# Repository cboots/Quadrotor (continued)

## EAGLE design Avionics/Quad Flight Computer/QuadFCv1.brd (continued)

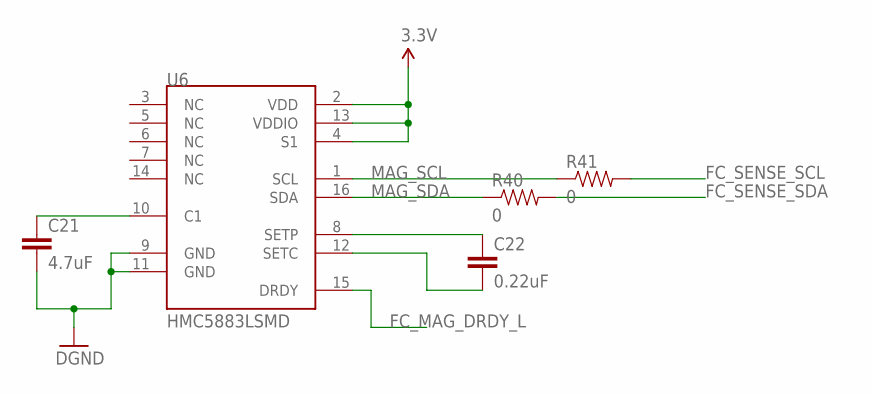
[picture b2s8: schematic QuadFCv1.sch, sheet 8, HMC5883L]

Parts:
C21: 4.7uF; 0402-CAP
C22: 0.22uF; 0402-CAP
R40, R41: 0; 0402-RES
U6: HMC5883LSMD; 16LPCC

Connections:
3.3V: U6.2 (VDD), U6.4 (S1), U6.13 (VDDIO); also elsewhere on the board
FC_MAG_DRDY_L: U6.15 (DRDY); also elsewhere on the board
FC_SENSE_SCL: R41.2; also elsewhere on the board
FC_SENSE_SDA: R40.2; also elsewhere on the board
GND: C21.2, U6.9 (GND), U6.11 (GND); also elsewhere on the board
MAG_SCL: R41.1, U6.1 (SCL); also elsewhere on the board
MAG_SDA: R40.1, U6.16 (SDA); also elsewhere on the board
unnamed: C21.1, U6.10 (C1)
unnamed: C22.1, U6.8 (SETP)
unnamed: C22.2, U6.12 (SETC)

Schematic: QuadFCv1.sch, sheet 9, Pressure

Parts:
C23: 0.1uF; 0402-CAP
U7: MS5611-01BA

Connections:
3.3V: C23.1, U7.1 (VDD), U7.2 (PS); also elsewhere on the board
FC_SENSE_SCL: U7.8 (SCLK); also elsewhere on the board
FC_SENSE_SDA: U7.7 (SDI/SDA); also elsewhere on the board
GND: C23.2, U7.3 (GND), U7.5 (CSB2); also elsewhere on the board

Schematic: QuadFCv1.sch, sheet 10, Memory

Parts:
J2: 1050270001
U8: 74AUP1G19GW; SOT363_PHILIPS
U9: S25FL127S; SOIC8

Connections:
3.3V: J2.P4 (VDD), U8.5 (VCC), U9.8 (VCC); also elsewhere on the board
FC_MEM_CLK: J2.P5 (SCLK), U9.6 (SCK); also elsewhere on the board
FC_MEM_FSS: U8.3 (EN_L); also elsewhere on the board
FC_MEM_MISO: J2.P7 (DAT0/DO), U9.2 (SO); also elsewhere on the board
FC_MEM_MOSI: J2.P3 (CMD/DI), U9.5 (SI); also elsewhere on the board
FC_MEM_SEL: U8.1 (SEL); also elsewhere on the board
FC_SD_PRESENT: J2.G1 (SWITCH); also elsewhere on the board
FLASH_CS_L: U8.6 (1Y), U9.1 (CS_L)
GND: J2.P6 (VSS1), U8.2 (GND), U9.4 (GND); also elsewhere on the board
SD_CS_L: J2.P2 (CD/DAT3/CS), U8.4 (2Y)

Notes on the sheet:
Internal Pullups

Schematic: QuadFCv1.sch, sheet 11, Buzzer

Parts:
BZR: CMT-1203-SMT
R57: 0; 0402-RES
R58, R59: 10K; 0402-RES
U4: MCP6L91T-E/OT; SOT23-5

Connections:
3.3V: R58.2; also elsewhere on the board
5V: U4.5 (V+); also elsewhere on the board
BUZZER_PWM: U4.3 (+IN); also elsewhere on the board
GND: BZR.P$2 (2), R59.1, U4.2 (V-); also elsewhere on the board
unnamed: R57.1, U4.1 (OUT)
unnamed: BZR.P$1 (1), R57.2
unnamed: R58.1, R59.2, U4.4 (-IN)

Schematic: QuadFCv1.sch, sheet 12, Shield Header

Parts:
JP1: M101X10-SMT-0.05; 1X10_SMT-0.05
JP2, JP3, JP4: M12; 1X12_SMT-0.05

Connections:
3.3V: JP3.2; also elsewhere on the board
5V: JP3.1; also elsewhere on the board
BUZZER_PWM: JP1.5; also elsewhere on the board
FC_IMU_MISO: JP2.2; also elsewhere on the board
FC_IMU_MOSI: JP2.1; also elsewhere on the board
FC_IMU_SCLK: JP2.3; also elsewhere on the board
FC_JTAG_TCK: JP4.5; also elsewhere on the board
FC_JTAG_TDI: JP4.7; also elsewhere on the board
FC_JTAG_TDO: JP4.8; also elsewhere on the board
FC_JTAG_TMS: JP4.6; also elsewhere on the board
FC_MEM_CLK: JP3.4; also elsewhere on the board
FC_MEM_MISO: JP3.5; also elsewhere on the board
FC_MEM_MOSI: JP3.3; also elsewhere on the board
FC_PB2: JP4.12; also elsewhere on the board
FC_PB3: JP4.11; also elsewhere on the board
FC_PB4: JP4.1; also elsewhere on the board
FC_PB5: JP4.2; also elsewhere on the board
FC_PD0: JP3.9; also elsewhere on the board
FC_PD1: JP3.8; also elsewhere on the board
FC_PD2: JP3.7; also elsewhere on the board
FC_PD3: JP3.6; also elsewhere on the board
FC_PD4: JP3.12; also elsewhere on the board
FC_PE4: JP3.10; also elsewhere on the board
FC_PE5: JP3.11; also elsewhere on the board
FC_PF0: JP2.5; also elsewhere on the board
FC_PF1: JP2.6; also elsewhere on the board
FC_PF2: JP2.7; also elsewhere on the board
FC_PF3: JP2.8; also elsewhere on the board
FC_PF4: JP2.4; also elsewhere on the board
FC_PG2: JP2.10; also elsewhere on the board
FC_PG3: JP2.9; also elsewhere on the board
FC_PG4: JP4.10; also elsewhere on the board
FC_PG5: JP4.9; also elsewhere on the board
FC_PG6: JP4.4; also elsewhere on the board
FC_PG7: JP4.3; also elsewhere on the board
FC_RESET_L: JP1.10; also elsewhere on the board
FC_SENSE_SCL: JP2.11; also elsewhere on the board
FC_SENSE_SDA: JP2.12; also elsewhere on the board
GND: JP1.1, JP1.2; also elsewhere on the board
GPS_RX: JP1.6; also elsewhere on the board
GPS_TX: JP1.7; also elsewhere on the board
RADIO_RX: JP1.3; also elsewhere on the board
RADIO_TX: JP1.4; also elsewhere on the board

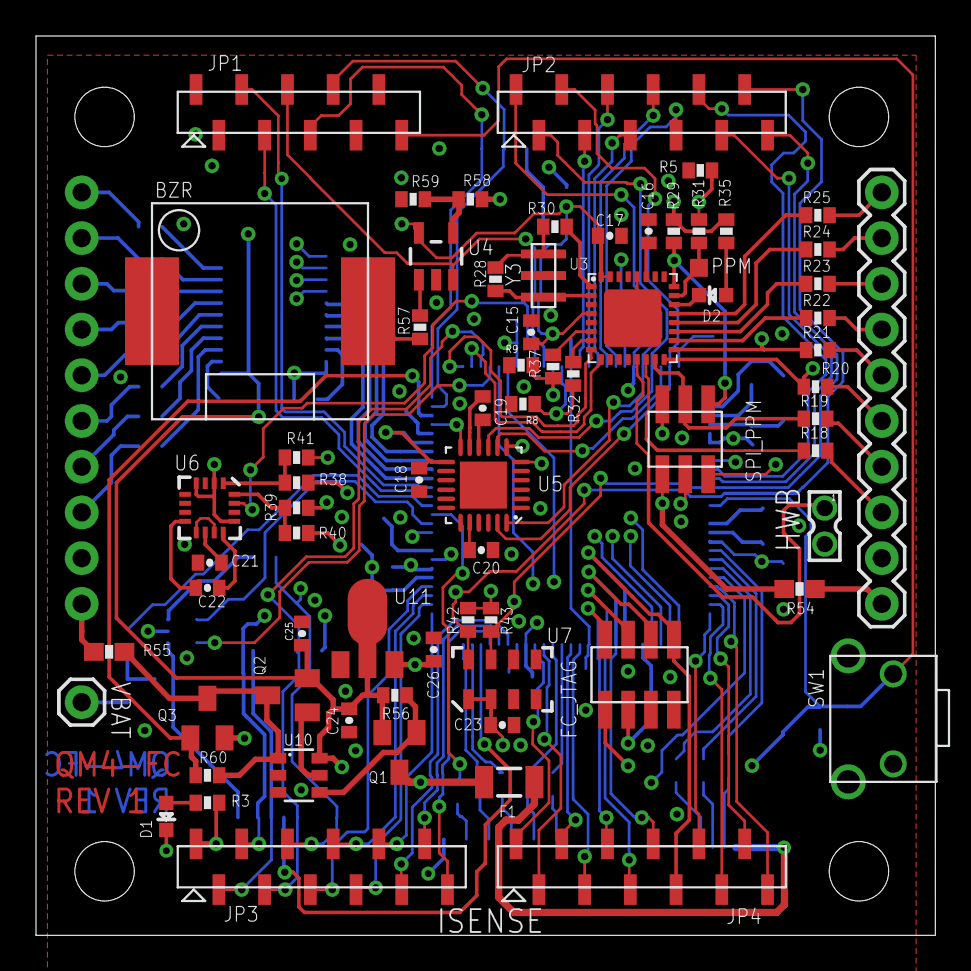
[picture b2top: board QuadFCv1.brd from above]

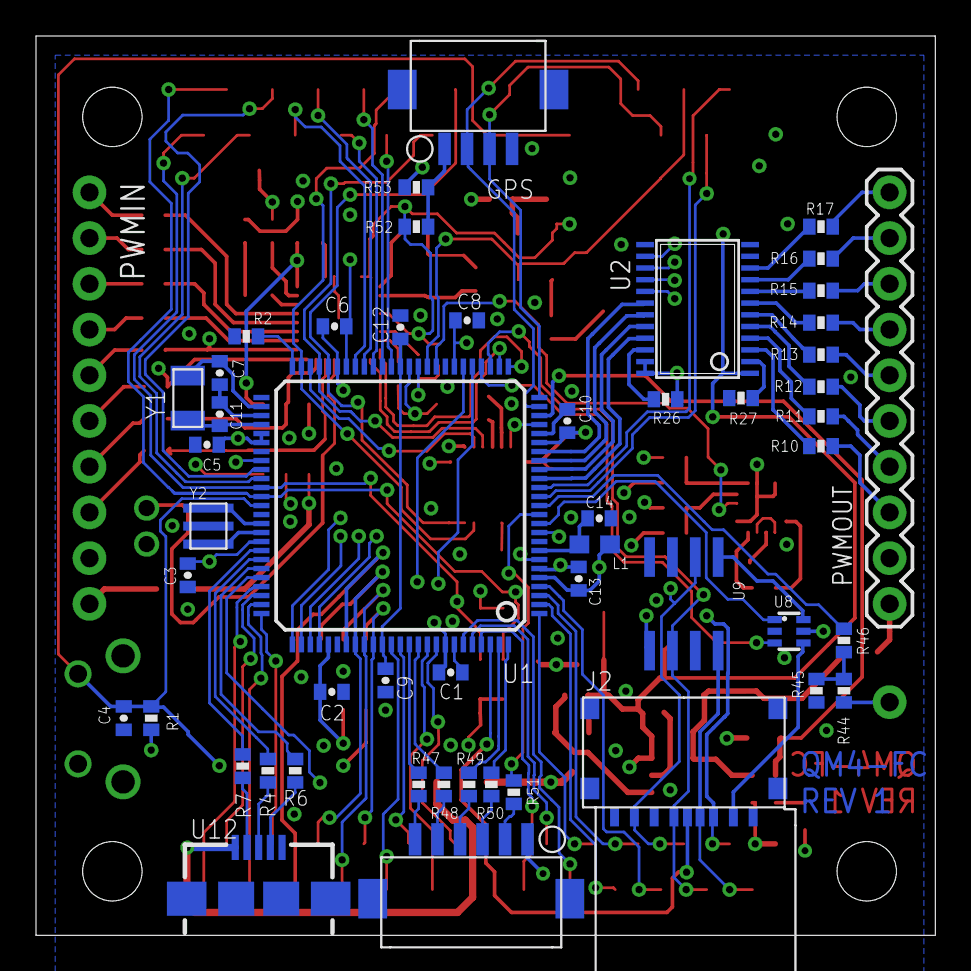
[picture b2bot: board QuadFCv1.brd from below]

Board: 4 copper layers, 50.0 x 50.0 mm, 125 parts (51 on the bottom side), 158 nets.

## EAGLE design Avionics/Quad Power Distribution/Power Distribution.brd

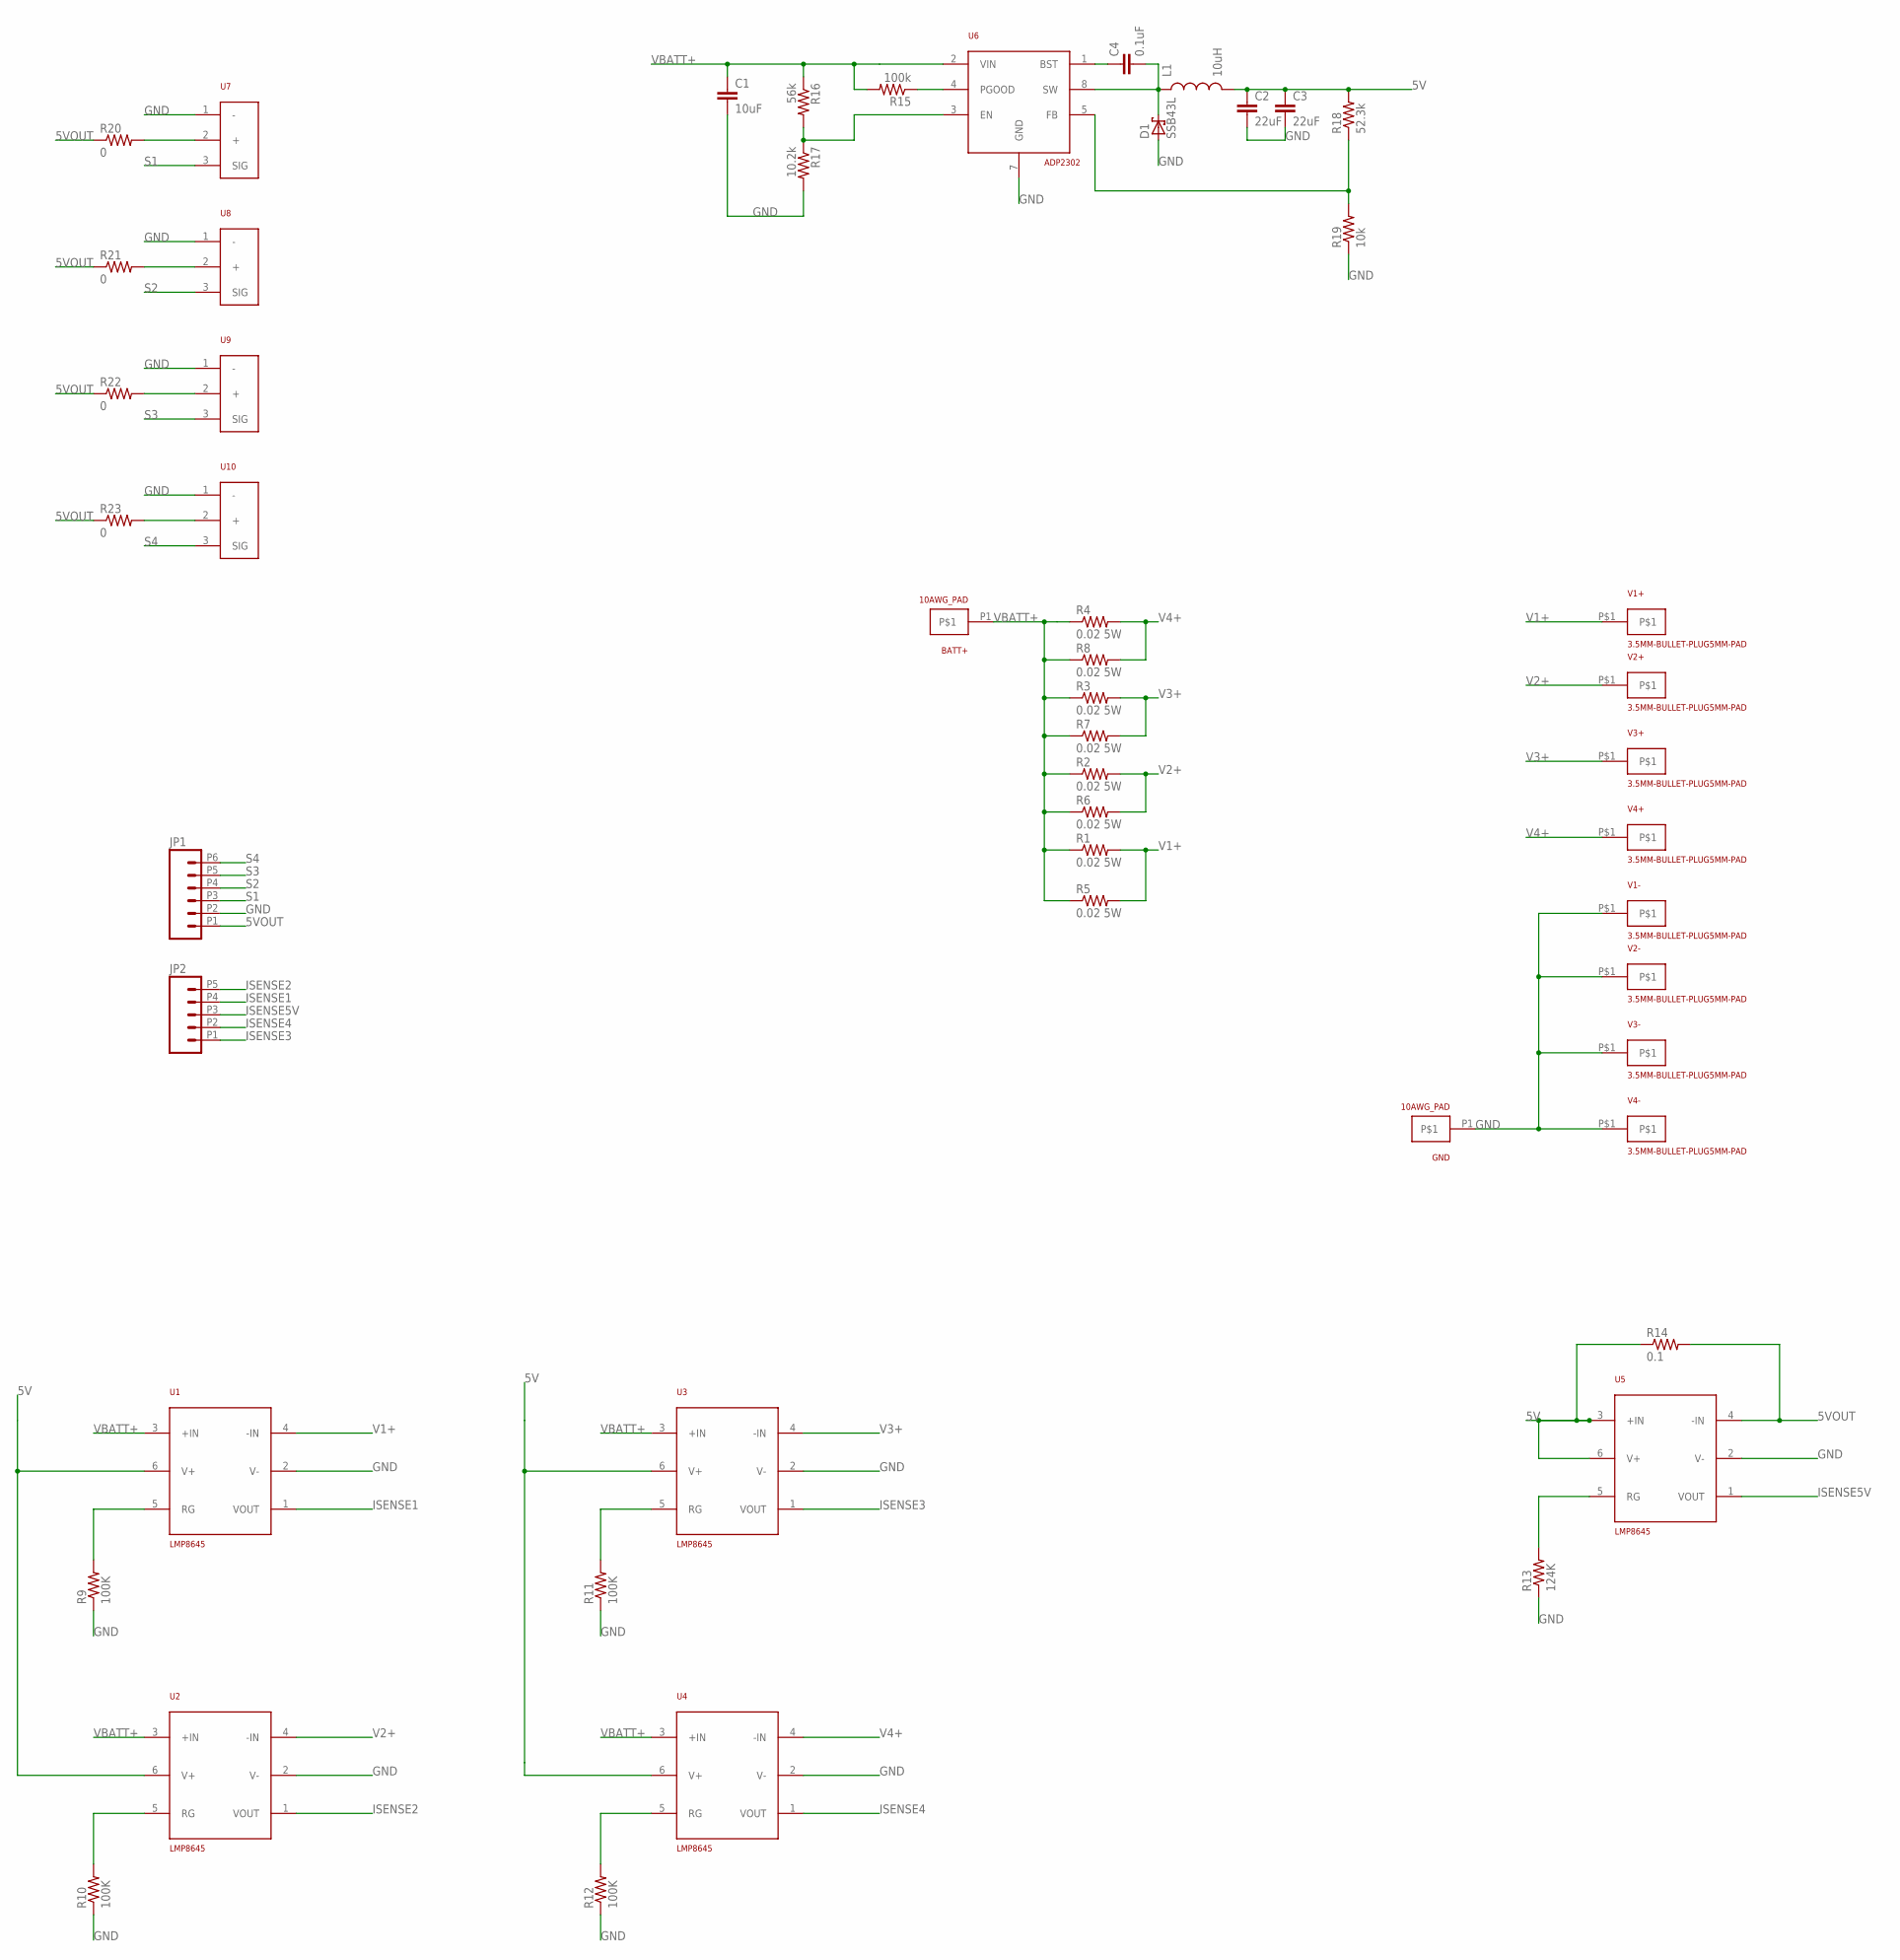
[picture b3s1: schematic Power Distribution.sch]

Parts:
BATT+: 10AWG_PAD; 10AWG_SOLDERPAD
C1: 10uF; 0603-CAP
C2, C3: 22uF; 0603-CAP
C4: 0.1uF; 0603-CAP
D1: SSB43L; SMB
GND: 10AWG_PAD; 10AWG_SOLDERPAD
JP1: M06DF13; DF13A-6P-1.25H
JP2: M05DF13; DF13A-5P-1.25H
L1: 10uH; 0603
R1, R2, R3, R4, R5, R6, R7, R8: 0.02 5W; R2512
R9, R10, R11, R12: 100K; 0603-RES
R13: 124K; 0603-RES
R14: 0.1; 0603-RES
R15: 100k; 0603-RES
R16: 56k; 0603-RES
R17: 10.2k; 0603-RES
R18: 52.3k; 0603-RES
R19: 10k; 0603-RES
R20, R21, R22, R23: 0; 0603-RES
U1, U2, U3, U4, U5: LMP8645; SOT23-6
U6: ADP2302; SOIC8
U7, U8, U9, U10: SERVOPLUGTHROUGHHOLE_0.1PITCH; 0.1-PITCH-3CONN_RANGLE
V1+, V1-, V2+, V2-, V3+, V3-, V4+, V4-: 3.5MM-BULLET-PLUG5MM-PAD; 5MMPLUG

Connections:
5V: C2.1, C3.1, L1.2, R14.1, R18.2, U1.6 (V+), U2.6 (V+), U3.6 (V+), U4.6 (V+), U5.3 (+IN), U5.6 (V+)
5VOUT: JP1.P1 (1), R14.2, R20.1, R21.1, R22.1, R23.1, U5.4 (-IN)
GND: C1.2, C2.2, C3.2, D1.A, GND.P1, JP1.P2 (2), R9.1, R10.1, R11.1, R12.1, R13.1, R17.2, R19.1, U1.2 (V-), U2.2 (V-), U3.2 (V-), U4.2 (V-), U5.2 (V-), U6.7 (GND), U7.1 (-), U8.1 (-), U9.1 (-), U10.1 (-), V1-.P$1, V2-.P$1, V3-.P$1, V4-.P$1
ISENSE1: JP2.P4 (4), U1.1 (VOUT)
ISENSE2: JP2.P5 (5), U2.1 (VOUT)
ISENSE3: JP2.P1 (1), U3.1 (VOUT)
ISENSE4: JP2.P2 (2), U4.1 (VOUT)
ISENSE5V: JP2.P3 (3), U5.1 (VOUT)
unnamed: R10.2, U2.5 (RG)
unnamed: R9.2, U1.5 (RG)
unnamed: R11.2, U3.5 (RG)
unnamed: R12.2, U4.5 (RG)
unnamed: R13.2, U5.5 (RG)
unnamed: C4.1, U6.1 (BST)
unnamed: C4.2, D1.C, L1.1, U6.8 (SW)
unnamed: R20.2, U7.2 (+)
unnamed: R18.1, R19.2, U6.5 (FB)
unnamed: R15.1, U6.4 (PGOOD)
unnamed: R16.2, R17.1, U6.3 (EN)
unnamed: R21.2, U8.2 (+)
unnamed: R22.2, U9.2 (+)
unnamed: R23.2, U10.2 (+)
S1: JP1.P3 (3), U7.3 (SIG)
S2: JP1.P4 (4), U8.3 (SIG)
S3: JP1.P5 (5), U9.3 (SIG)
S4: JP1.P6 (6), U10.3 (SIG)
V1+: R1.2, R5.2, U1.4 (-IN), V1+.P$1
V2+: R2.2, R6.2, U2.4 (-IN), V2+.P$1
V3+: R3.2, R7.2, U3.4 (-IN), V3+.P$1
V4+: R4.2, R8.2, U4.4 (-IN), V4+.P$1
VBATT+: BATT+.P1, C1.1, R1.1, R2.1, R3.1, R4.1, R5.1, R6.1, R7.1, R8.1, R15.2, R16.1, U1.3 (+IN), U2.3 (+IN), U3.3 (+IN), U4.3 (+IN), U6.2 (VIN)

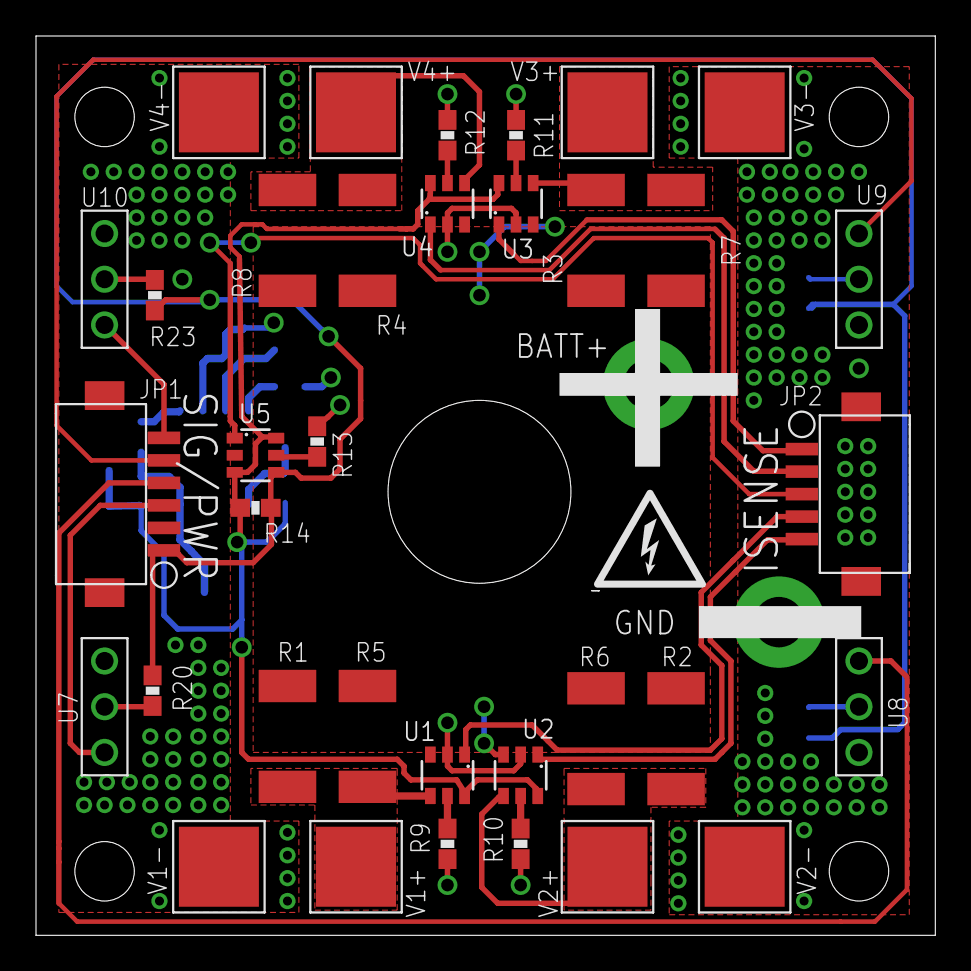
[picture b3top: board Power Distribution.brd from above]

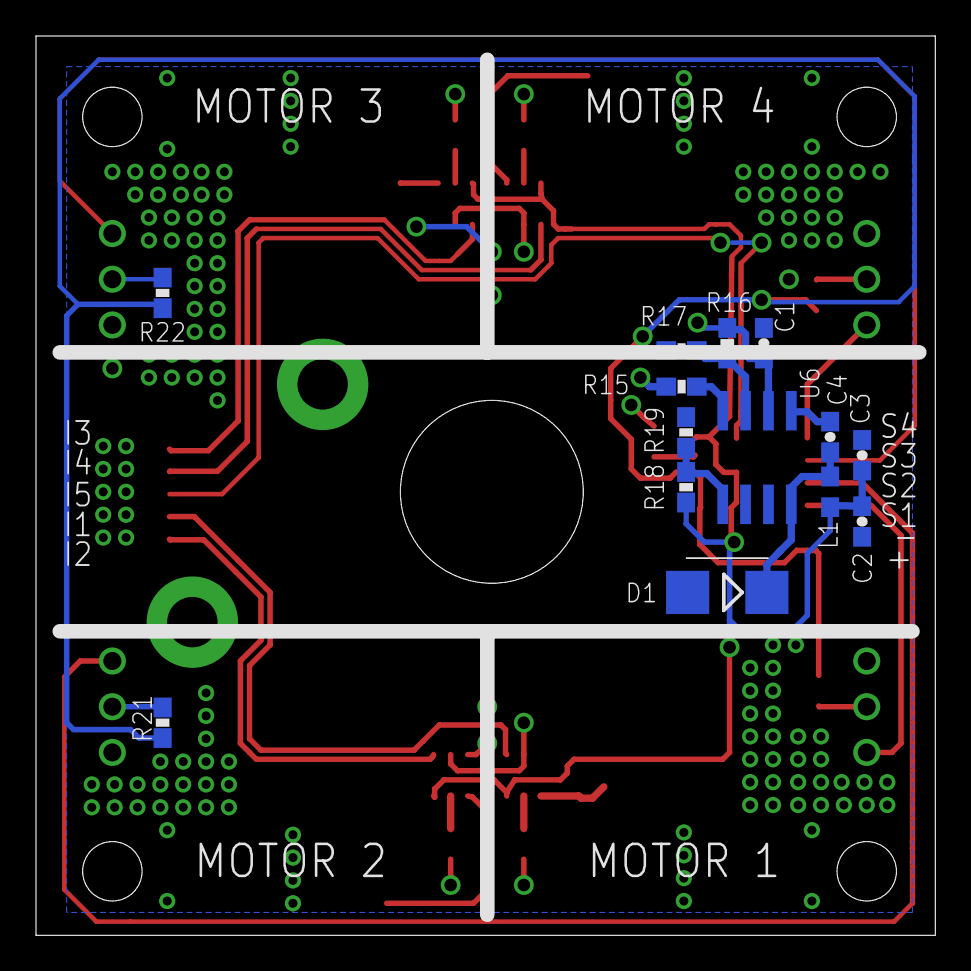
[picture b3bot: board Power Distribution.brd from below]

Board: 2 copper layers, 50.0 x 50.0 mm, 56 parts (14 on the bottom side), 31 nets.

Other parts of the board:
U$1, U$2, U$3, U$4: STAND-OFF
U$5: SHOCK_HAZARD

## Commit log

2013-06-15 Added directory structure and start of airframe assembly.
2013-06-15 Added more detail to the assembly. Now contains estimates of body, booms, motor mounts, and landing struts.
2013-06-15 Committed updated parts lib
2013-06-15 Commited directory structure.
2013-06-15 Added placeholder ESC's to the assembly.
    Committed System Block Diagram
2013-06-16 Added zipties to ESC Detailed notes on drawing
2013-06-16 Added chart of naming conventions for quadrotor body frame.
2013-06-17 Added start of Power Distribution board
2013-06-19 Added current sense circuits and most of the switching regulator.
    Need to add signal splitters and output pins.
2013-06-21 Finished switcher circuit, almost there.
2013-06-26 Completed layout and routing. Adding vias later
2013-06-26 Cleaned up silk
2013-06-26 Added more silk and changed vias to tented small circles
2013-06-27 Committed file outputs and cleaned silk. Added shock hazard symbol
2013-06-27 Committed final version of power distribution board and added to sketchup assembly.
2013-06-30 Added Cortex M3 chip to library
    Started schematic for flight computer.
2013-07-03 Added LPC4337 to library. Damn that took a long time
2013-07-14 Broke out all of the flight computer MCU ports and assigned the dedicated signals for use internally.
2013-07-14 Pin Assignments for FC MCU
2013-07-14 Added PPM encoder framework from Ardupilot mega schematic
2013-07-18 Added IMU. Needs some work
2013-07-19 Exported all parts to libraries. Replaced IMU with MPU-6000.
2013-07-21 Connected sensor network and added pressure sensor
2013-07-21 Added 16MB flash chip for core event logging and mission profile configuration. Internal EEPROM will be used for core configuration (failsafe modes, dead zones, etc), external flash will store missio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
2013-07-21 Added Micro SD Card slot
2013-07-23 Added several connectors and modified power inputs to not immediately go to 5V plane.
2013-07-23 Replaced all parts with 0402 packages to save board space.
    I'm gonna need a smaller tweezers...
2013-07-24 Added power management circuitry
2013-07-26 Changed form factor of FC to be 1.95"x1.95" to be compliant with the power distribution board. Makes stacking and interconnectivity simpler.
2013-07-27 Consolidated entire design into single FC library. Makes everything neater and avoids package conflicts. Using any new package should be added to this library OR copied to it from another lib.
2013-07-27 Finished first attempt to layout EVERYTHING.
2013-07-27 Added EagleUP model libraries plus a few custom ones. Will be adding more models just to be cool.
2013-07-27 Migrated models to separate repo https://github.com/cboots/EagleUpModels.git
2013-07-27 Refactored power distrib board libraries into single library
2013-07-28 Updated board for model compatibility (no actual layout or part changes).
2013-07-28 Updated airframe with full 3D power board.
2013-07-28 Minor updates.
2013-07-28 Updated part references.
2013-07-28 Updated part references
2013-07-28 Updated Power Distribution Board with new detailed connector models
2013-07-29 Updated airframe with preliminary flight computer design.
2013-07-31 Added early sketch of pcb quad design to facilitate long term planning.
2013-07-31 Minor updates to PCB
2013-08-01 Added some connectors
2013-08-01 Saved positioning
2013-08-01 Updated PCBA model
2013-08-02 Finished pinout for shield headers
2013-08-02 Some progress on routing
2013-08-04 Lots more routing done
2013-08-04 More routing
2013-08-04 Only 4 wires left. Sooo close
2013-08-04 Finished routing and updated ariframe assembly
2013-08-04 Adjusted FC size to align with power board.
2013-08-04 Tracked down the last few airwires
2013-08-04 Cleaned up silkscreen and added part numbers.
2013-08-04 Added power on LED.
2013-08-04 Deleting extra backups
2013-08-06 Cleaned up silk, added missed layers, exported paste layers.
2013-08-07 Added sketch of sharp rangefinder sensor placement. Probably will not stay in this configuration, may not be tall enough to get over props. Also don't want the stack getting too tall or heavy. All sh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
2013-08-08 Changed model to X configuration. Software will eventually be able to handle both, but start with X.
    Added naming conventions for cross config
2013-08-11 Added a couple voltage dividers to make level shifts safer.
2013-08-29 Continuing to rework flight computer board.
2015-05-13 Added XMC4500-F100K1024 AB.lbr
2015-05-13 Started to revamp design.
2015-05-13 Fresh start. FU eagle.
2015-05-14 Added avionics library as Eagle-Library submodule.
2015-05-14 Added IMU to library
2015-05-15 Removed software directory
2015-05-15 Added barometer
2015-05-16 Added memory module
2015-05-17 Added radio part
2015-05-17 Updated git ignore
2015-05-25 Added radio components
2015-06-01 Added RF base station project
2015-06-05 Fixed library references and added balun to 2.4GHz circuit
2015-06-06 Applied DRU
2015-06-07 Added more updates to board layout.
2015-06-08 Finished first draft of 2.4GHz layout.
2015-06-09 Started to build 900MHz circuit
2017-02-16 Restarted as KiCad Project. KiCad is cool now.
2017-02-20 Added framework and started capturing radio schematics.
2017-02-20 Added more RF passives and placement of RF front ends
2017-02-21 Lots of power tree and layout work
2017-02-26 Restarted initial layout and cleaned up decoupling/RF layout.
2017-02-28 Nearly completed initial placement.
2017-03-03 Added additional pinout
2017-03-03 Wired up everything and started rearranging layout
2017-03-03 Finished breaking out signals to connector sheet and interconnecting processors.
2017-03-03 Fixed missing connections and did more layout
2017-03-03 Swapped some pins to make routing easier.
2017-03-04 Some more pin swapping and routing of signals. Placed reset pullup resistors.
2017-03-04 Cleaned up vias and DRC Errors
2017-03-04 Continuing to route out MCU signals.
2017-03-04 Did some more routing
2017-03-05 Additional routing
2017-03-05 Finished routing and DRC check.
2017-03-05 Cleaned up routing details and plane continuity problems.
2017-03-06 Fixed some grounding and routing. Moved USB input diode to top side to make reduced BOM easier.
2017-03-06 Silkscreen cleanup.
2017-03-06 Silkscreen and dimension drawing fixes
2017-03-07 Added LEDs
2017-03-07 Cleaned up silk and DRC for new components.
2017-03-08 Changed LED configuration, added smart driver chip to let all the CPUs access it..
2017-03-08 DFM/BOM Optimizations
2017-03-09 Added Logo, connected GPS SDA/SCL, and cleaned silk.
2017-03-09 Added option resistors for IMU to be connected to radio chips via I2C
2017-03-09 Added pullup to CS
2017-03-09 Fixed hopefully last DRC error.
2017-03-10 Built outputs and added manufacturing part numbers to make BOM search easier.
2017-03-10 Rebuilt output files and generated a few BOM fixes.
2017-03-10 Updated more manufacturing part numbers for macrofab compatibility.
2017-03-10 Fixed connector part number
2017-03-15 Finished rerouting and power supply update. Replaced connectors and did initial replacement.
2017-03-15 Reduced inductor size at small efficiency cost.
2017-03-16 Finished replacement and supply tuning
2017-03-16 Minor BOM fixes.
2017-03-16 Refactored repo into Navi repo
